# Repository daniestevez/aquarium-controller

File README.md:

# aquarium-controller
Arduino-based Aquarium controller

[More information](http://destevez.net/electronics-projects/arduino-aquarium-controller/)

Libraries required for the Arduino software:

* Time, DS1307RTC from http://playground.arduino.cc/Code/Time
* Timer from http://playground.arduino.cc/Code/Timer
* Timezone from https://github.com/JChristensen/Timezone
* Keypad from http://playground.arduino.cc/Code/Keypad
* U8glib from https://github.com/olikraus/u8glib
* OneWireNoResistor from https://github.com/bigjosh/OneWireNoResistor

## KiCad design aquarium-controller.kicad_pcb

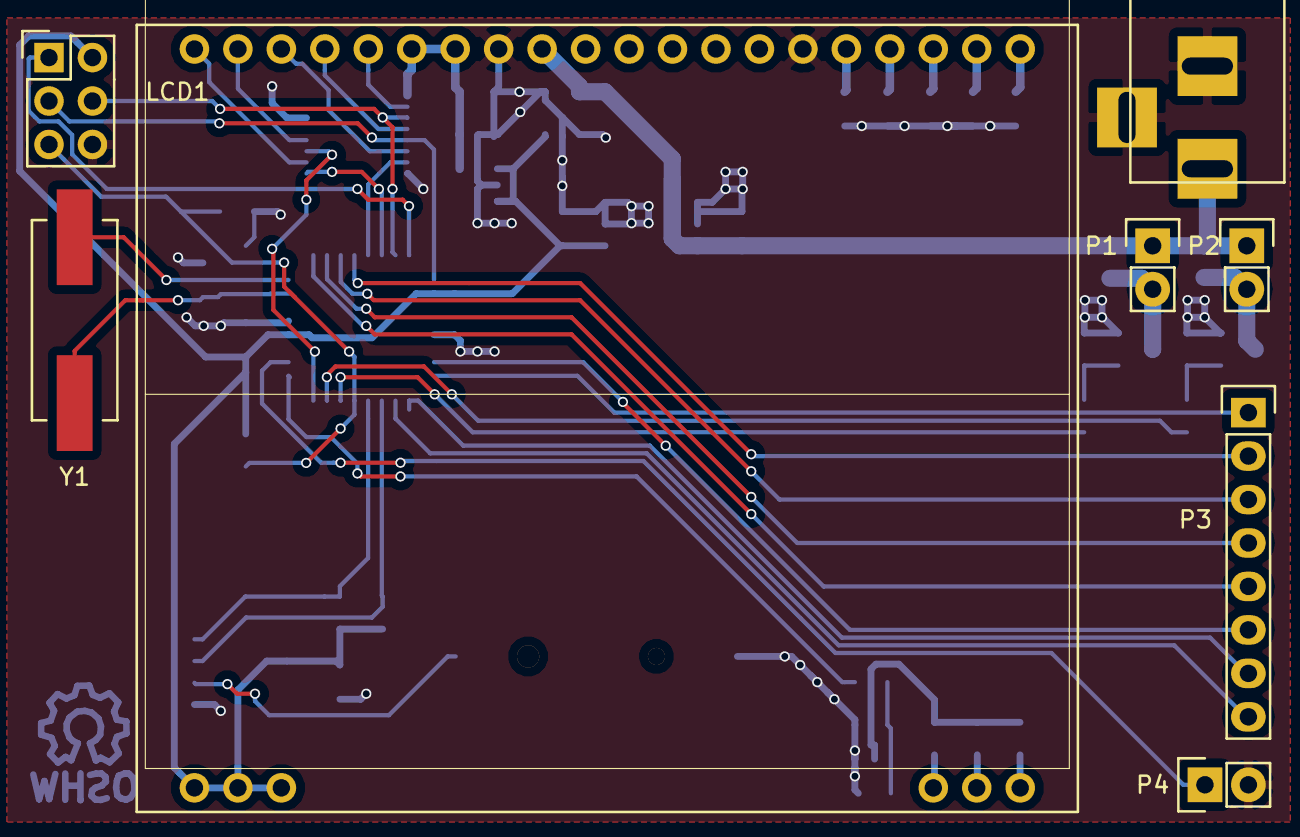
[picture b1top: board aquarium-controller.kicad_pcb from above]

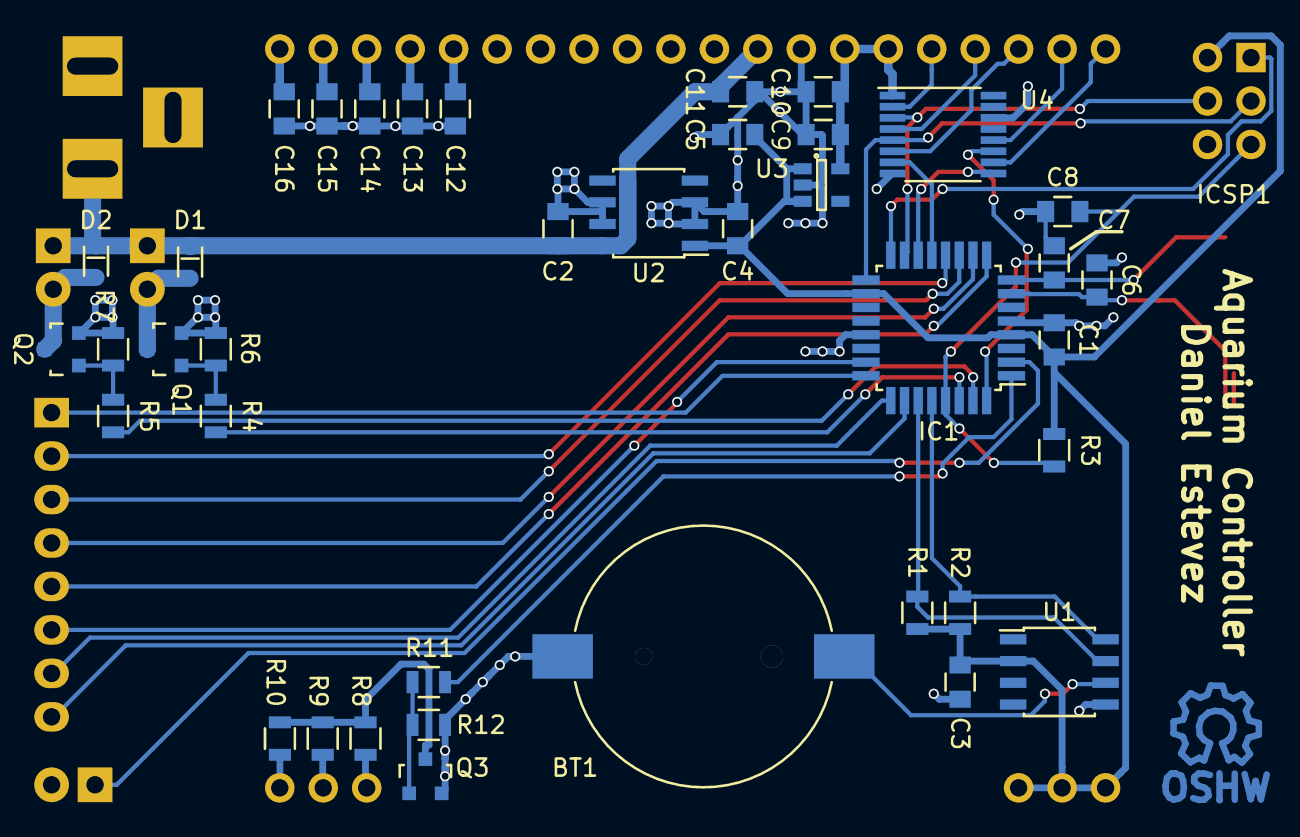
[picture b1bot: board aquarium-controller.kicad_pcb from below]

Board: 2 copper layers, 47 parts (39 on the bottom side), 47 nets.

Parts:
BT1: Battery; BC501SM
C1, C3, C4, C8, C10: 100n; C_0805
C2: 330n; C_0805
C5, C9, C11, C12, C13, C14, C15, C16: 1u; C_0805
C6, C7: 22p; C_0805
CON1: BARREL_JACK
D1, D2: DB2J20900L; SMini2-F5-B
IC1: ATMEGA328PB; TQFP-32_7x7mm_Pitch0.8mm
ICSP1: AVR-ISP-6; Pin_Header_Straight_2x03
LCD1: DOGM128-6; LED55X46
P1, P2, P4: CONN_01X02; Socket_Strip_Straight_1x02
P3: CONN_01X08; Socket_Strip_Straight_1x08
Q1, Q2, Q3: 2N7002E; SOT-23
R1, R2, R3: 10k; R_0805
R4, R5, R8, R9, R10, R11: 100; R_0805
R6, R7, R12: 100K; R_0805
U1: DS3231M; SOIC-8_3.9x4.9mm_Pitch1.27mm
U2: L78L05ACD; SOIC-8_3.9x4.9mm_Pitch1.27mm
U3: MIC5504; SOT-23-5
U4: 4050; TSSOP-16_4.4x5mm_Pitch0.65mm
Y1: 16MHz; Crystal_HC49-SD_SMD

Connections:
+3V3: C9.1, C10.1, LCD1.34, LCD1.35, U3.5, U4.1
+5V: C1.1, C3.2, C4.1, C5.1, IC1.4, IC1.18, ICSP1.2, LCD1.1, LCD1.2, LCD1.3, R1.1, R2.1, R3.1, U1.2, U2.1, U3.1, U3.3
+12V: C2.1, C11.1, CON1.1, D1.1, D2.1, LCD1.32, P1.1, P2.1, U2.8
/1WIRE: IC1.2, P4.1
/BACKLIGHT: IC1.1, R11.2
/COL1: IC1.26, P3.8
/COL2: IC1.25, P3.7
/COL3: IC1.23, P3.6
/COL4: IC1.9, P3.5
/HEATER: IC1.30, R4.2
/LCDA0: LCD1.38, U4.6
/LCDCS1B: LCD1.40, U4.10
/LCDRST: LCD1.39, U4.12
/LCDSCL: LCD1.37, U4.4
/LCDSI: LCD1.36, U4.2
/LIGHT: IC1.31, R5.2
/ROW1: IC1.10, P3.4
/ROW2: IC1.11, P3.3
/ROW3: IC1.12, P3.2
/ROW4: IC1.24, P3.1
/SCL: IC1.28, R2.2, U1.8
/SDA: IC1.27, R1.2, U1.7
GND: BT1.2, C1.2, C2.2, C3.1, C4.2, C5.2, C6.2, C7.2, C8.2, C9.2, C10.2, C11.2, C12.1, C13.1, C14.1, C15.1, C16.1, CON1.2, CON1.3, IC1.5, IC1.21, ICSP1.6, LCD1.26, LCD1.33, P4.2, Q1.2, Q2.2, Q3.2, R6.2, R7.2, R12.2, U1.5, U2.2, U2.3, U2.6, U2.7, U3.2, U4.8, U4.14
unnamed: BT1.1, U1.6
unnamed: C6.1, IC1.7, Y1.2
unnamed: C7.1, IC1.8, Y1.1
unnamed: C8.1, IC1.29, ICSP1.5, R3.2
unnamed: C12.2, LCD1.25
unnamed: C13.2, LCD1.24
unnamed: C14.2, LCD1.23
unnamed: C15.2, LCD1.22
unnamed: C16.2, LCD1.21
unnamed: D1.2, P1.2, Q1.3
unnamed: D2.2, P2.2, Q2.3
unnamed: IC1.13, U4.7
unnamed: IC1.14, U4.9
unnamed: IC1.15, ICSP1.4, U4.3
unnamed: IC1.16, ICSP1.1
unnamed: IC1.17, ICSP1.3, U4.5
unnamed: IC1.32, U4.11
unnamed: LCD1.18, R8.2
unnamed: LCD1.19, R9.2
unnamed: LCD1.20, R10.2
unnamed: Q1.1, R4.1, R6.1
unnamed: Q2.1, R5.1, R7.1
unnamed: Q3.1, R11.1, R12.1
unnamed: Q3.3, R8.1, R9.1, R10.1

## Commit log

2016-04-16 Imported revision A
2016-06-13 Moved Kicad files into hardware folder
2016-06-13 Imported arduino software for the controller
2016-06-13 Updated README with required Arduino libraries
2017-01-20 Added link to my blog in the README
2018-01-09 Moved Arduino files to aquarium_controller folder to please Arduino IDE
2018-01-12 Port to u8g2
2018-01-12 Added AVR WDT
2018-01-12 Added compiled firmware and fuses
2018-05-22 Add temperature sensor consistency check
    Do not turn on heater if sensor seems to have failed (i.e., reports a very low temperature)
2019-03-10 Error checking for temperature sensors
2019-03-10 Corrected typo in interface message
2019-03-10 Updated firmware build
2019-05-12 Fixed bug in temperature sensor CRC check
